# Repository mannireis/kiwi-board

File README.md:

# Kiwi Board

The Kiwi Board is a 42-key split keyboard designed for stenographic input. It features a 3×6 column-staggered layout with 3 thumb keys per side.  
The design is based on the [Polyglot keyboard](https://stenokeyboards.com/products/polyglot-keyboard) and includes an integrated RP2040 microcontroller.

This project started after I discovered steno and wanted to build a keyboard tailored for learning and experimenting with chorded input.

---

## Specifications

- Layout: Split, 3×6 + 3 thumb keys per side
- Total keys: 42
- Switches: MX
- Microcontroller: RP2040 (integrated)
- Firmware: [RMK](https://rmk.rs/) — A feature-rich Rust keyboard firmware
- Intended use: Compatible with steno software (e.g. [Plover](https://www.openstenoproject.org/plover/))

---

## Images

### PCB

### Schematic

### Case

---

## Bill of Materials (BOM)

| Item         | Price   | Notes                                |
|--------------|---------|--------------------------------------|
| PCB          | $83.78  | Ordered from JLCPCB                  |
| Keycaps      | $9.90   | [AliExpress link](https://shorturl.at/fVK32) |
| Rubber Feet  | $3.84   | [AliExpress link](https://shorturl.at/bqHlW) |
| Switches     | $32.72  | [Deltakey Co.](https://deltakeyco.com/)     |
| diodes    |  |           i own them           |
| hotswap sockets    |  |           i have them               |
| **Total**    | **$130.24** |                              |

---

## Firmware

The Kiwi Board uses [RMK](https://rmk.rs/), A feature-rich Rust keyboard firmware!

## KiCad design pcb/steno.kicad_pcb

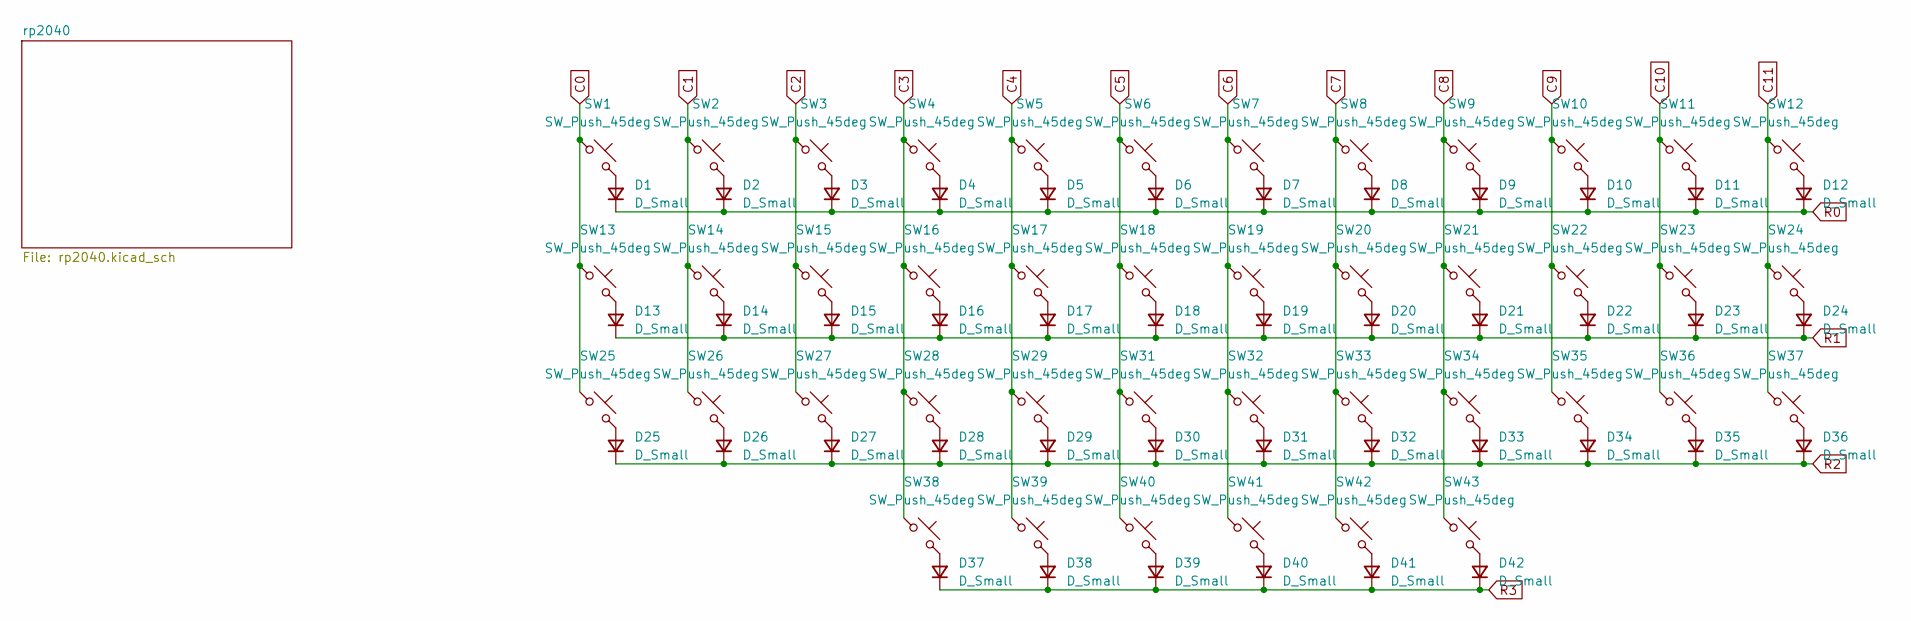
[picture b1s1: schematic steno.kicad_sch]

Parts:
D1, D2, D3, D4, D5, D6, D7, D8, D9, D10, D11, D12, D13, D14, D15, D16, D17, D18, D19, D20, D21, D22, D23, D24, D25, D26, D27, D28, D29, D30, D31, D32, D33, D34, D35, D36, D37, D38, D39, D40, D41, D42: D_Small; D_DO-35_SOD27_P7.62mm_Horizontal
SW1, SW2, SW3, SW4, SW5, SW6, SW7, SW8, SW9, SW10, SW11, SW12, SW13, SW14, SW15, SW16, SW17, SW18, SW19, SW20, SW21, SW22, SW23, SW24, SW25, SW26, SW27, SW28, SW29, SW31, SW32, SW33, SW34, SW35, SW36, SW37, SW38, SW39, SW40, SW41, SW42, SW43: SW_Push_45deg; MX-Hotswap-1U

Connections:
C0: SW1.1, SW13.1, SW25.1; also elsewhere on the board
C1: SW2.1, SW14.1, SW26.1; also elsewhere on the board
C2: SW3.1, SW15.1, SW27.1; also elsewhere on the board
C3: SW4.1, SW16.1, SW28.1, SW38.1; also elsewhere on the board
C4: SW5.1, SW17.1, SW29.1, SW39.1; also elsewhere on the board
C5: SW6.1, SW18.1, SW31.1, SW40.1; also elsewhere on the board
C6: SW7.1, SW19.1, SW32.1, SW41.1; also elsewhere on the board
C7: SW8.1, SW20.1, SW33.1, SW42.1; also elsewhere on the board
C8: SW9.1, SW21.1, SW34.1, SW43.1; also elsewhere on the board
C9: SW10.1, SW22.1, SW35.1; also elsewhere on the board
C10: SW11.1, SW23.1, SW36.1; also elsewhere on the board
C11: SW12.1, SW24.1, SW37.1; also elsewhere on the board
unnamed: D1.2 (A), SW1.2
unnamed: D2.2 (A), SW2.2
unnamed: D3.2 (A), SW3.2
unnamed: D4.2 (A), SW4.2
unnamed: D5.2 (A), SW5.2
unnamed: D6.2 (A), SW6.2
unnamed: D7.2 (A), SW7.2
unnamed: D8.2 (A), SW8.2
unnamed: D9.2 (A), SW9.2
unnamed: D10.2 (A), SW10.2
unnamed: D11.2 (A), SW11.2
unnamed: D12.2 (A), SW12.2
unnamed: D13.2 (A), SW13.2
unnamed: D14.2 (A), SW14.2
unnamed: D15.2 (A), SW15.2
unnamed: D16.2 (A), SW16.2
unnamed: D17.2 (A), SW17.2
unnamed: D18.2 (A), SW18.2
unnamed: D19.2 (A), SW19.2
unnamed: D20.2 (A), SW20.2
unnamed: D21.2 (A), SW21.2
unnamed: D22.2 (A), SW22.2
unnamed: D23.2 (A), SW23.2
unnamed: D24.2 (A), SW24.2
unnamed: D25.2 (A), SW25.2
unnamed: D26.2 (A), SW26.2
unnamed: D27.2 (A), SW27.2
unnamed: D28.2 (A), SW28.2
unnamed: D29.2 (A), SW29.2
unnamed: D30.2 (A), SW31.2
unnamed: D31.2 (A), SW32.2
unnamed: D32.2 (A), SW33.2
unnamed: D33.2 (A), SW34.2
unnamed: D34.2 (A), SW35.2
unnamed: D35.2 (A), SW36.2
unnamed: D36.2 (A), SW37.2
unnamed: D37.2 (A), SW38.2
unnamed: D38.2 (A), SW39.2
unnamed: D39.2 (A), SW40.2
unnamed: D40.2 (A), SW41.2
unnamed: D41.2 (A), SW42.2
unnamed: D42.2 (A), SW43.2
R0: D1.1 (K), D2.1 (K), D3.1 (K), D4.1 (K), D5.1 (K), D6.1 (K), D7.1 (K), D8.1 (K), D9.1 (K), D10.1 (K), D11.1 (K), D12.1 (K); also elsewhere on the board
R1: D13.1 (K), D14.1 (K), D15.1 (K), D16.1 (K), D17.1 (K), D18.1 (K), D19.1 (K), D20.1 (K), D21.1 (K), D22.1 (K), D23.1 (K), D24.1 (K); also elsewhere on the board
R2: D25.1 (K), D26.1 (K), D27.1 (K), D28.1 (K), D29.1 (K), D30.1 (K), D31.1 (K), D32.1 (K), D33.1 (K), D34.1 (K), D35.1 (K), D36.1 (K); also elsewhere on the board
R3: D37.1 (K), D38.1 (K), D39.1 (K), D40.1 (K), D41.1 (K), D42.1 (K); also elsewhere on the board

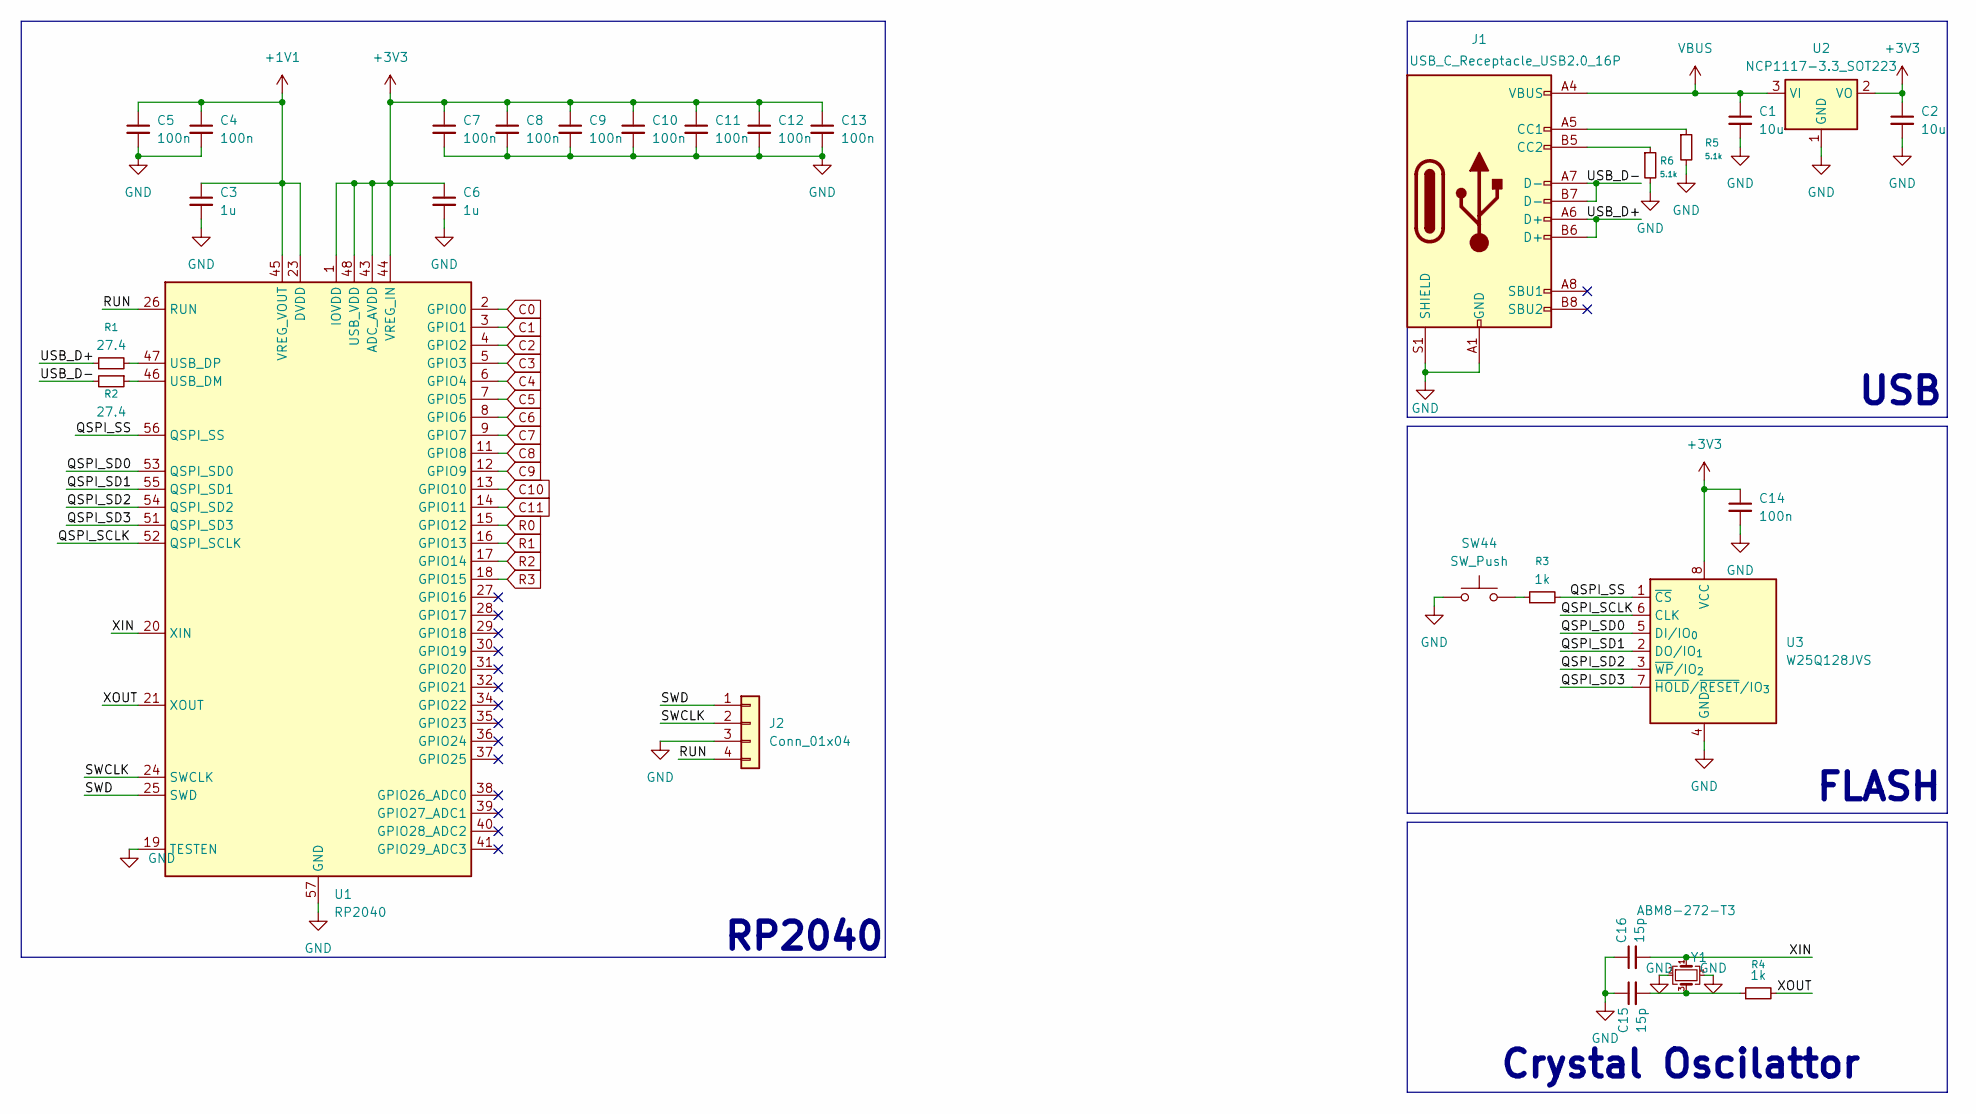
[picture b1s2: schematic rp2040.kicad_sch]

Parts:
C1, C2: 10u; C_0402_1005Metric
C3, C6: 1u; C_0402_1005Metric
C4, C5, C7, C8, C9, C10, C11, C12, C13, C14: 100n; C_0402_1005Metric
C15, C16: 15p; C_0402_1005Metric
J1: USB_C_Receptacle_USB2.0_16P; USB_C_Receptacle_HCTL_HC-TYPE-C-16P-01A
J2: Conn_01x04; PinHeader_1x04_P2.54mm_Vertical
R1, R2: 27.4; R_0402_1005Metric
R3, R4: 1k; R_0402_1005Metric
R5, R6: 5.1k; R_0402_1005Metric
SW44: SW_Push; SW_Push_1P1T_NO_CK_KMR2
U1: RP2040; QFN-56-1EP_7x7mm_P0.4mm_EP3.2x3.2mm
U2: NCP1117-3.3_SOT223; SOT-223-3_TabPin2
U3: W25Q128JVS; SOIC-8_5.3x5.3mm_P1.27mm
Y1: ABM8-272-T3; Crystal_SMD_Abracon_ABM8AIG-4Pin_3.2x2.5mm

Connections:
+1V1: C3.1, C4.1, C5.1, U1.23 (DVDD), U1.45 (VREG_VOUT), U1.50 (DVDD)
+3V3: C2.1, C6.1, C7.1, C8.1, C9.1, C10.1, C11.1, C12.1, C13.1, C14.1, U1.1 (IOVDD), U1.10 (IOVDD), U1.22 (IOVDD), U1.33 (IOVDD), U1.42 (IOVDD), U1.43 (ADC_AVDD), U1.44 (VREG_IN), U1.48 (USB_VDD), U1.49 (IOVDD), U2.2 (VO), U3.8 (VCC)
/rp2040/QSPI_SCLK: U1.52 (QSPI_SCLK), U3.6 (CLK)
/rp2040/QSPI_SD0: U1.53 (QSPI_SD0), U3.5 (DI/IO_{0})
/rp2040/QSPI_SD1: U1.55 (QSPI_SD1), U3.2 (DO/IO_{1})
/rp2040/QSPI_SD2: U1.54 (QSPI_SD2), U3.3 (~WP/IO_{2})
/rp2040/QSPI_SD3: U1.51 (QSPI_SD3), U3.7 (~HOLD/~RESET/IO_{3})
/rp2040/QSPI_SS: R3.2, U1.56 (QSPI_SS), U3.1 (~CS)
/rp2040/RUN: J2.4, U1.26 (RUN)
/rp2040/SWCLK: J2.2, U1.24 (SWCLK)
/rp2040/SWD: J2.1, U1.25 (SWD)
/rp2040/USB_D+: J1.A6 (D+), J1.B6 (D+), R1.1
/rp2040/USB_D-: J1.A7 (D-), J1.B7 (D-), R2.2
/rp2040/XIN: C16.2, U1.20 (XIN), Y1.1
/rp2040/XOUT: R4.2, U1.21 (XOUT)
C0: U1.2 (GPIO0); also elsewhere on the board
C1: U1.3 (GPIO1); also elsewhere on the board
C2: U1.4 (GPIO2); also elsewhere on the board
C3: U1.5 (GPIO3); also elsewhere on the board
C4: U1.6 (GPIO4); also elsewhere on the board
C5: U1.7 (GPIO5); also elsewhere on the board
C6: U1.8 (GPIO6); also elsewhere on the board
C7: U1.9 (GPIO7); also elsewhere on the board
C8: U1.11 (GPIO8); also elsewhere on the board
C9: U1.12 (GPIO9); also elsewhere on the board
C10: U1.13 (GPIO10); also elsewhere on the board
C11: U1.14 (GPIO11); also elsewhere on the board
GND: C1.2, C2.2, C3.2, C4.2, C5.2, C6.2, C7.2, C8.2, C9.2, C10.2, C11.2, C12.2, C13.2, C14.2, C15.1, C16.1, J1.A1 (GND), J1.A12 (GND), J1.B1 (GND), J1.B12 (GND), J1.S1 (SHIELD), J2.3, R5.2, R6.2, SW44.1, U1.19 (TESTEN), U1.57 (GND), U2.1 (GND), U3.4 (GND), Y1.2, Y1.4
unnamed: C15.2, R4.1, Y1.3
unnamed: J1.A5 (CC1), R5.1
unnamed: J1.B5 (CC2), R6.1
unnamed: R3.1, SW44.2
unnamed: R2.1, U1.46 (USB_DM)
unnamed: R1.2, U1.47 (USB_DP)
R0: U1.15 (GPIO12); also elsewhere on the board
R1: U1.16 (GPIO13); also elsewhere on the board
R2: U1.17 (GPIO14); also elsewhere on the board
R3: U1.18 (GPIO15); also elsewhere on the board
VBUS: C1.1, J1.A4 (VBUS), J1.A9 (VBUS), J1.B4 (VBUS), J1.B9 (VBUS), U2.3 (VI)

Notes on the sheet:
USB
FLASH
RP2040
Crystal Oscilattor

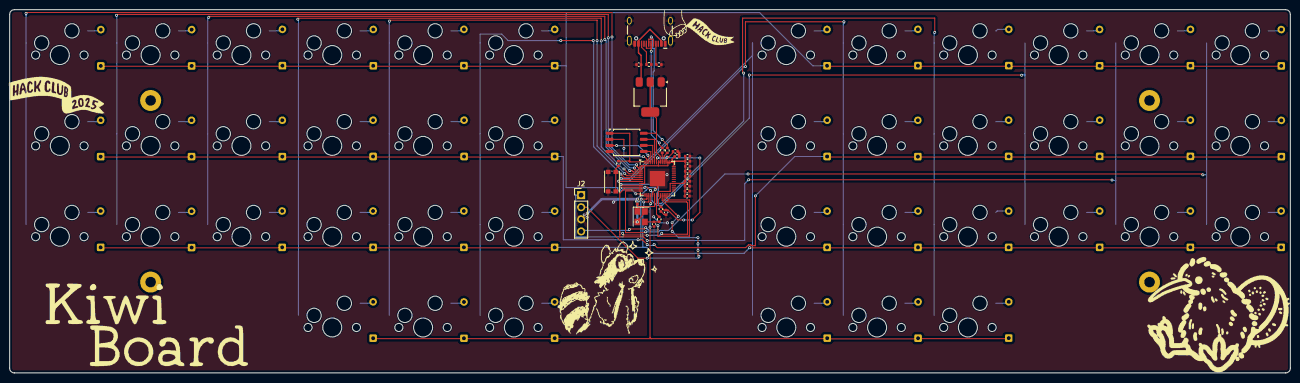
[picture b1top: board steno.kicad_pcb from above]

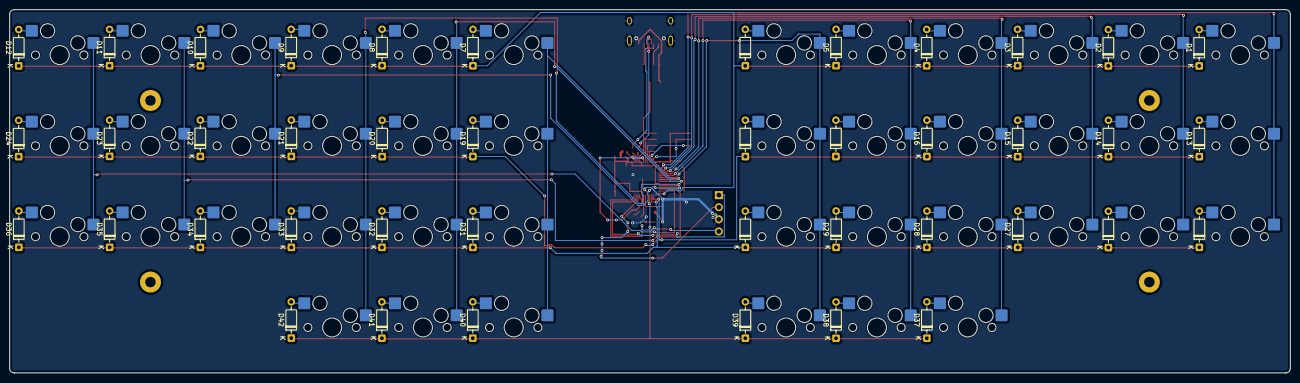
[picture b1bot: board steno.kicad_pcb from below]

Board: 2 copper layers, 268.7 x 76.2 mm, 113 parts (84 on the bottom side), 81 nets.

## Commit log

2025-07-24 add JOURNAL and write JOURNAL
2025-07-24 add stuff to journal
2025-07-25 test
2025-07-26 Add 3D files!
    Finished my case fuck yeah
2025-07-27 add pcb stuff
2025-07-27 add firmware
2025-08-03 add images
